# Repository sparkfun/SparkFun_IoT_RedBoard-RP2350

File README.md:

[*SparkFun IoT RedBoard - RP2350 (WRL-27708)*](https://www.sparkfun.com/sparkfun-iot-redboard-rp2350.html)

The SparkFun IoT Redboard - RP2350 combines the RP2350 microcontroller with the Raspberry Pi Radio Module 2 to provide a powerful and versatile wireless development platform in the Arduino R4 form factor. This IoT Redboard also includes integrated battery power and charging circuits, &micro;SD card slot, Qwiic connector, 3-pin debug header as well as a 22-pin ribbon cable connector tied to the RP2350's HSTX (high-speed transmit) pins. The board shares a pinout between female headers and matching 0.1"-spaced plated through-hole (PTH) headers to allow you to choose between temporary or soldered connections. 

Repository Contents
-------------------

* **/Documentation** - Data sheets, additional product information
* **/Examples** - Example code
* **/Hardware** - Eagle design files (.brd, .sch)
* **/docs** - GitHub Pages documentation files

Documentation
--------------

* **[Hookup Guide](https://docs.sparkfun.com/SparkFun_IoT_RedBoard-RP2350/)** - Basic hookup guide for the SparkFun IoT RedBoard - RP2350.

Product Versions
----------------

* [WRL-27708](https://www.sparkfun.com/sparkfun-iot-redboard-rp2350.html) - Initial release of the IoT RedBoard - RP2350

License Information
-------------------

This product is ***open source***!

Please review the LICENSE.md file for license information.

If you have any questions or concerns on licensing, please contact technical support on our [SparkFun forums](https://forum.sparkfun.com/viewforum.php?f=152).

Distributed as-is; no warranty is given.

* Your friends at SparkFun.

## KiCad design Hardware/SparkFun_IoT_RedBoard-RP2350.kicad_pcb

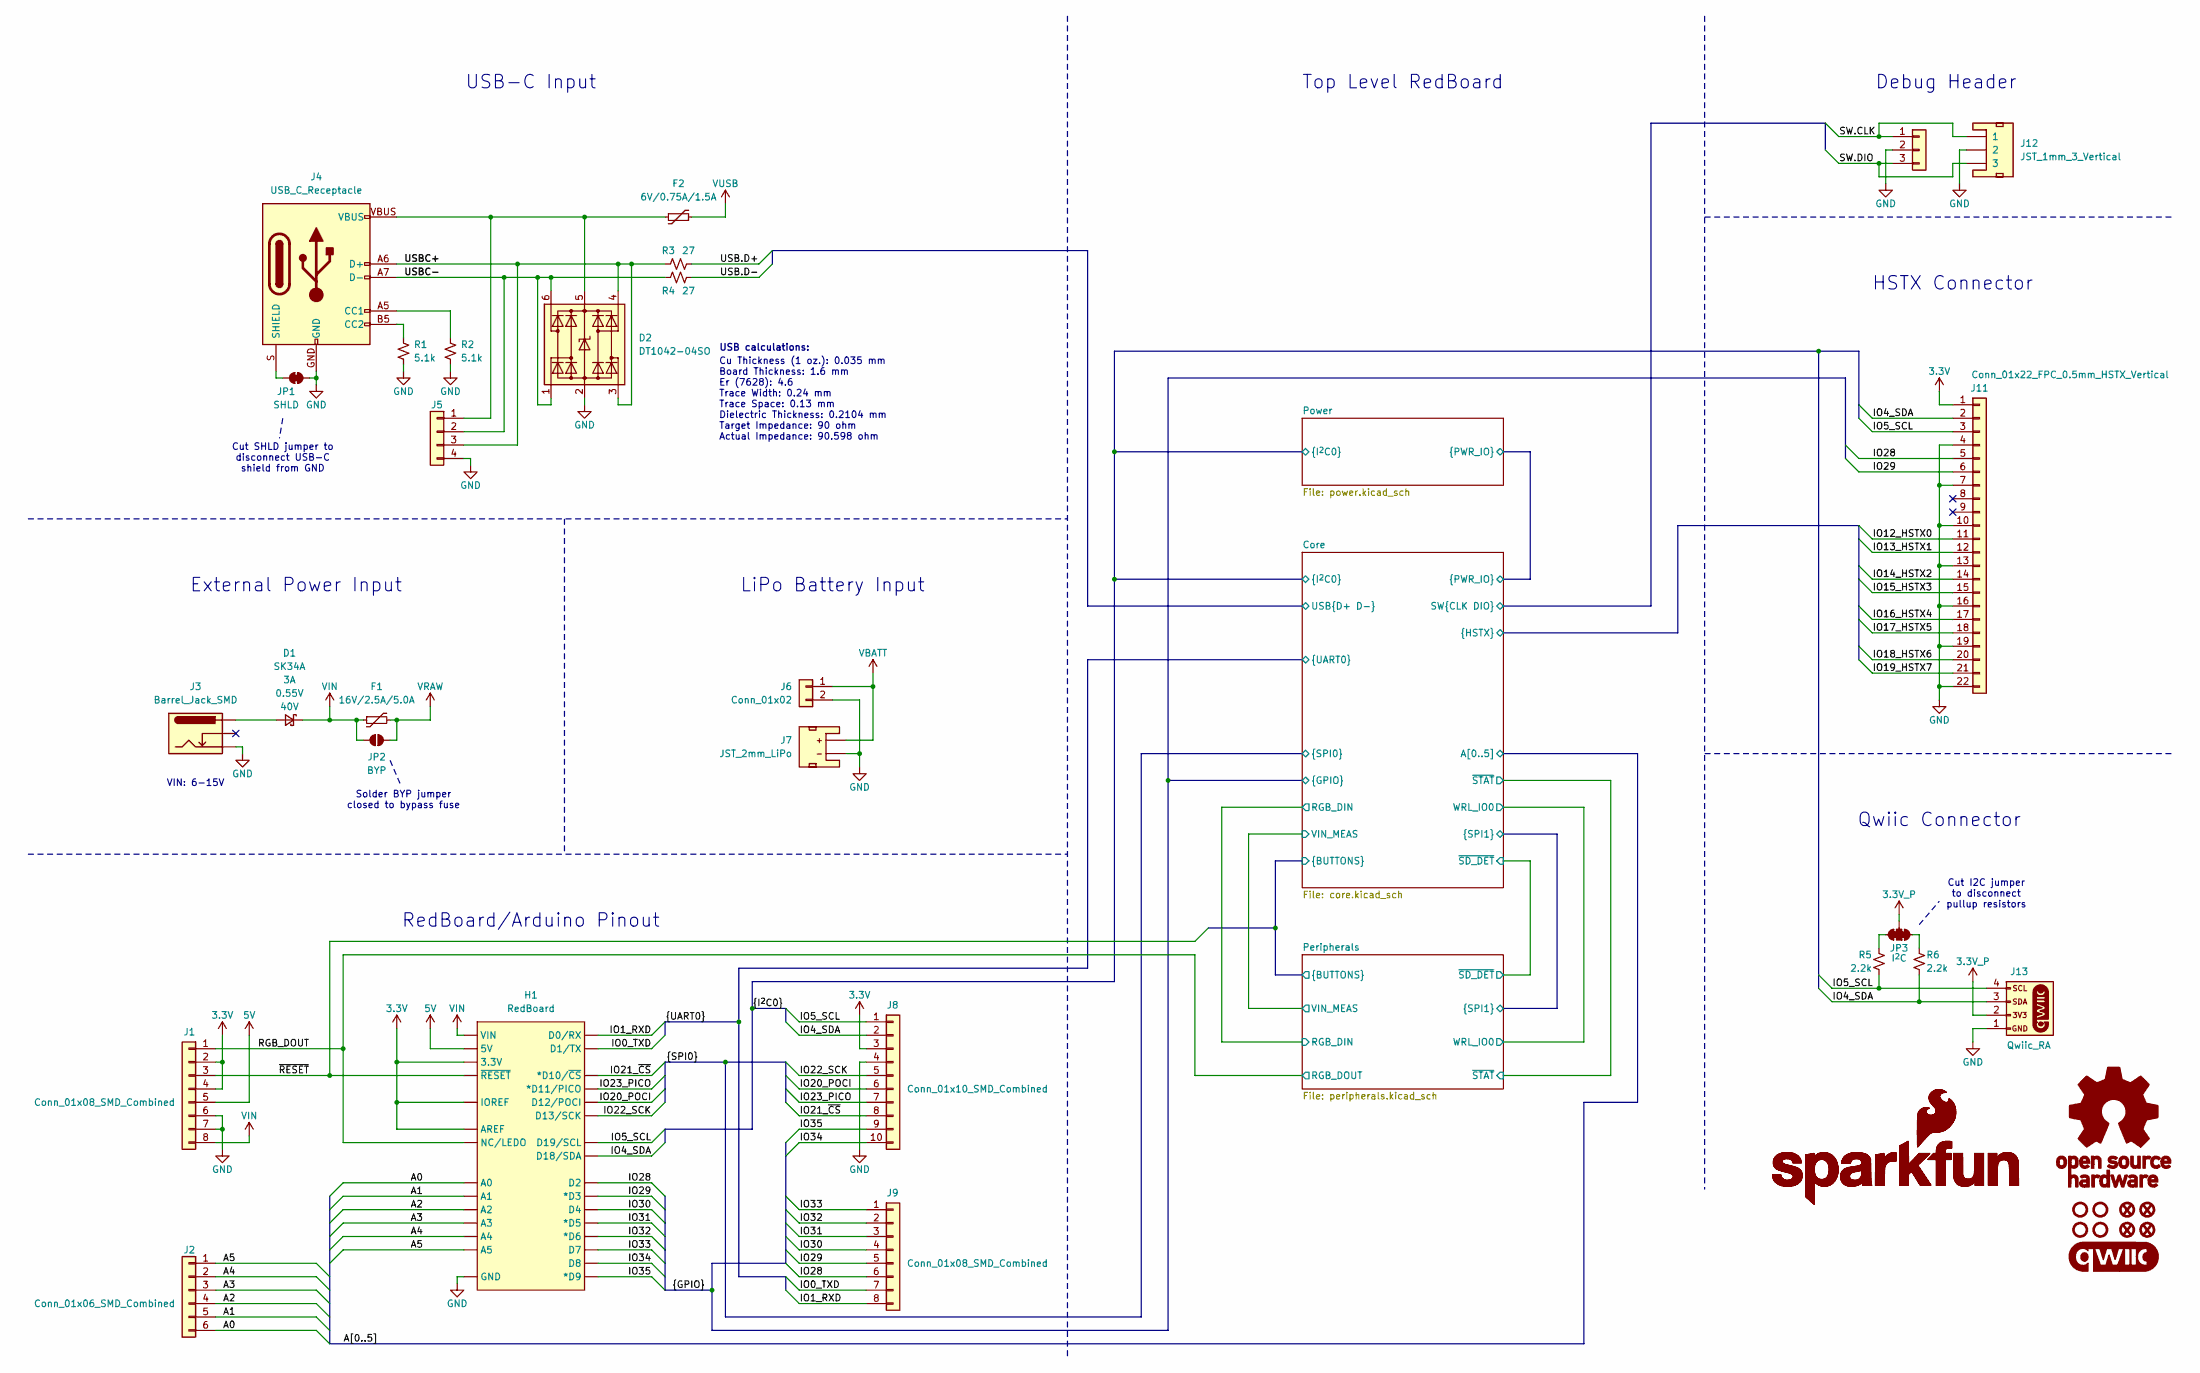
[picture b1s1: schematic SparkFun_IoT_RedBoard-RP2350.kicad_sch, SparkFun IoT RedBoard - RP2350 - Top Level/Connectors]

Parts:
D1: SK34A; SMA
D2: DT1042-04SO; SOT23-6
F1: 16V/2.5A/5.0A; 1812
F2: 6V/0.75A/1.5A; 1206
FID1, FID2, FID3, FID4: Fiducial_0.5mm; Fiducial_0.5mm_Mask1mm
G1: SparkFun_Logo; SparkFun_Logo_8mm
G2: SparkFun_Logo
G3: OSHW_Logo; Creative_Commons_License
G4: qwiic_Logo
H1: RedBoard
J1, J9: Conn_01x08_SMD_Combined; 1x08_SMD_Combined
J2: Conn_01x06_SMD_Combined; 1x06_SMD_Combined
J3: Barrel_Jack_SMD; Power_Jack_SMD
J4: USB_C_Receptacle; USB-C_16
J5: Conn_01x04_SolderPads; 1x04_Solder_Pads
J6: Conn_01x02; 1x02
J7: JST_2mm_LiPo; JST_SMD_2.0mm-2
J8: Conn_01x10_SMD_Combined; 1x10_SMD_Combined
J10: Conn_01x03; 1x03
J11: Conn_01x22_FPC_0.5mm_HSTX_Vertical; FPC_0.5mm-22_Vertical
J12: JST_1mm_3_Vertical; JST_SMD_1.0mm-3_Vertical
J13: Qwiic_RA; JST_SMD_1.0mm-4_RA
JP1: SHLD; Jumper_2_NC_Trace
JP2: BYP; Jumper_2_NO
JP3: I^{2}C; Jumper_3_NC-2_Trace
R1, R2: 5.1k; R_0402_1005Metric
R3, R4: 27; R_0402_1005Metric
R5, R6: 2.2k; R_0402_1005Metric
ST1, ST2, ST3, ST4: Standoff

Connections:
3.3V: H1.3.3V, H1.AREF, H1.IOREF, J1.2, J1.4, J8.3, J11.1; also elsewhere on the board
3.3V_P: J13.2, JP3.2 (B); also elsewhere on the board
5V: H1.5V, J1.5; also elsewhere on the board
/A0: H1.A0, J2.6; also elsewhere on the board
/A1: H1.A1, J2.5; also elsewhere on the board
/A2: H1.A2, J2.4; also elsewhere on the board
/A3: H1.A3, J2.3; also elsewhere on the board
/A4: H1.A4, J2.2; also elsewhere on the board
/A5: H1.A5, J2.1; also elsewhere on the board
/Core/IO12_HSTX0: J11.11; also elsewhere on the board
/Core/IO13_HSTX1: J11.12; also elsewhere on the board
/Core/IO14_HSTX2: J11.14; also elsewhere on the board
/Core/IO15_HSTX3: J11.15; also elsewhere on the board
/Core/IO16_HSTX4: J11.17; also elsewhere on the board
/Core/IO17_HSTX5: J11.18; also elsewhere on the board
/Core/IO18_HSTX6: J11.20; also elsewhere on the board
/Core/IO19_HSTX7: J11.21; also elsewhere on the board
/Core/SW.CLK: J10.1, J12.1; also elsewhere on the board
/Core/SW.DIO: J10.3, J12.3; also elsewhere on the board
/Core/USB.D+: R3.2; also elsewhere on the board
/Core/USB.D-: R4.2; also elsewhere on the board
/Core/~RESET: H1.~{RESET}, J1.3; also elsewhere on the board
/IO0_TXD: H1.D1 (D1/TX), J9.7; also elsewhere on the board
/IO1_RXD: H1.D0 (D0/RX), J9.8; also elsewhere on the board
/IO4_SDA: H1.D18 (D18/SDA), J8.2, J11.2, J13.3, R6.1; also elsewhere on the board
/IO5_SCL: H1.D19 (D19/SCL), J8.1, J11.3, J13.4, R5.1; also elsewhere on the board
/IO20_POCI: H1.D12 (D12/POCI), J8.6; also elsewhere on the board
/IO21_~CS: H1.D10 (*D10/~CS), J8.8; also elsewhere on the board
/IO22_SCK: H1.D13 (D13/SCK), J8.5; also elsewhere on the board
/IO23_PICO: H1.D11 (*D11/PICO), J8.7; also elsewhere on the board
/IO28: H1.D2, J9.6, J11.5; also elsewhere on the board
/IO29: H1.D3 (*D3), J9.5, J11.6; also elsewhere on the board
/IO30: H1.D4, J9.4; also elsewhere on the board
/IO31: H1.D5 (*D5), J9.3; also elsewhere on the board
/IO32: H1.D6 (*D6), J9.2; also elsewhere on the board
/IO33: H1.D7, J9.1; also elsewhere on the board
/IO34: H1.D8, J8.10; also elsewhere on the board
/IO35: H1.D9 (*D9), J8.9; also elsewhere on the board
/RGB_DOUT: H1.NC/LEDO, J1.1; also elsewhere on the board
/USBC+: D2.3 (I/O2), D2.4 (I/O3), J4.A6 (D+), J4.B6 (D+), J5.3, R3.1
/USBC-: D2.1 (I/O1), D2.6 (I/O4), J4.A7 (D-), J4.B7 (D-), J5.2, R4.1
GND: D2.2 (GND), H1.GND, J1.6, J1.7, J3.GND, J4.GND, J5.4, J6.2, J7.1 (-), J8.4, J10.2, J11.4, J11.7, J11.10, J11.13, J11.16, J11.19, J11.22, J12.2, J13.1, JP1.2 (B), R1.1, R2.1; also elsewhere on the board
unnamed: D1.A, J3.PWR
unnamed: D2.5 (VCC), F2.1, J4.VBUS, J5.1
unnamed: J4.A5 (CC1), R2.2
unnamed: J4.B5 (CC2), R1.2
unnamed: J4.S (SHIELD), JP1.1 (A)
unnamed: JP3.1 (A), R6.2
unnamed: JP3.3 (C), R5.2
VBATT: J6.1, J7.2 (+); also elsewhere on the board
VIN: D1.C (K), F1.1, H1.VIN, J1.8, JP2.1 (A)
VRAW: F1.2, JP2.2 (B); also elsewhere on the board
VUSB: F2.2; also elsewhere on the board

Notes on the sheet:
Qwiic Connector
Top Level RedBoard
Cut SHLD jumper to disconnect USB-C shield from GND
USB calculations:
VIN: 6-15V
Debug Header
External Power Input
Cut I2C jumper to disconnect pullup resistors
HSTX Connector
RedBoard/Arduino Pinout
USB-C Input
LiPo Battery Input
Cu Thickness (1 oz.): 0.035 mm Board Thickness: 1.6 mm Er (7628): 4.6 Trace Width: 0.24 mm Trace Space: 0.13 mm Dielectric Thickness: 0.2104 mm Target Impedance: 90 ohm Actual Impedance: 90.598 ohm
Solder BYP jumper closed to bypass fuse

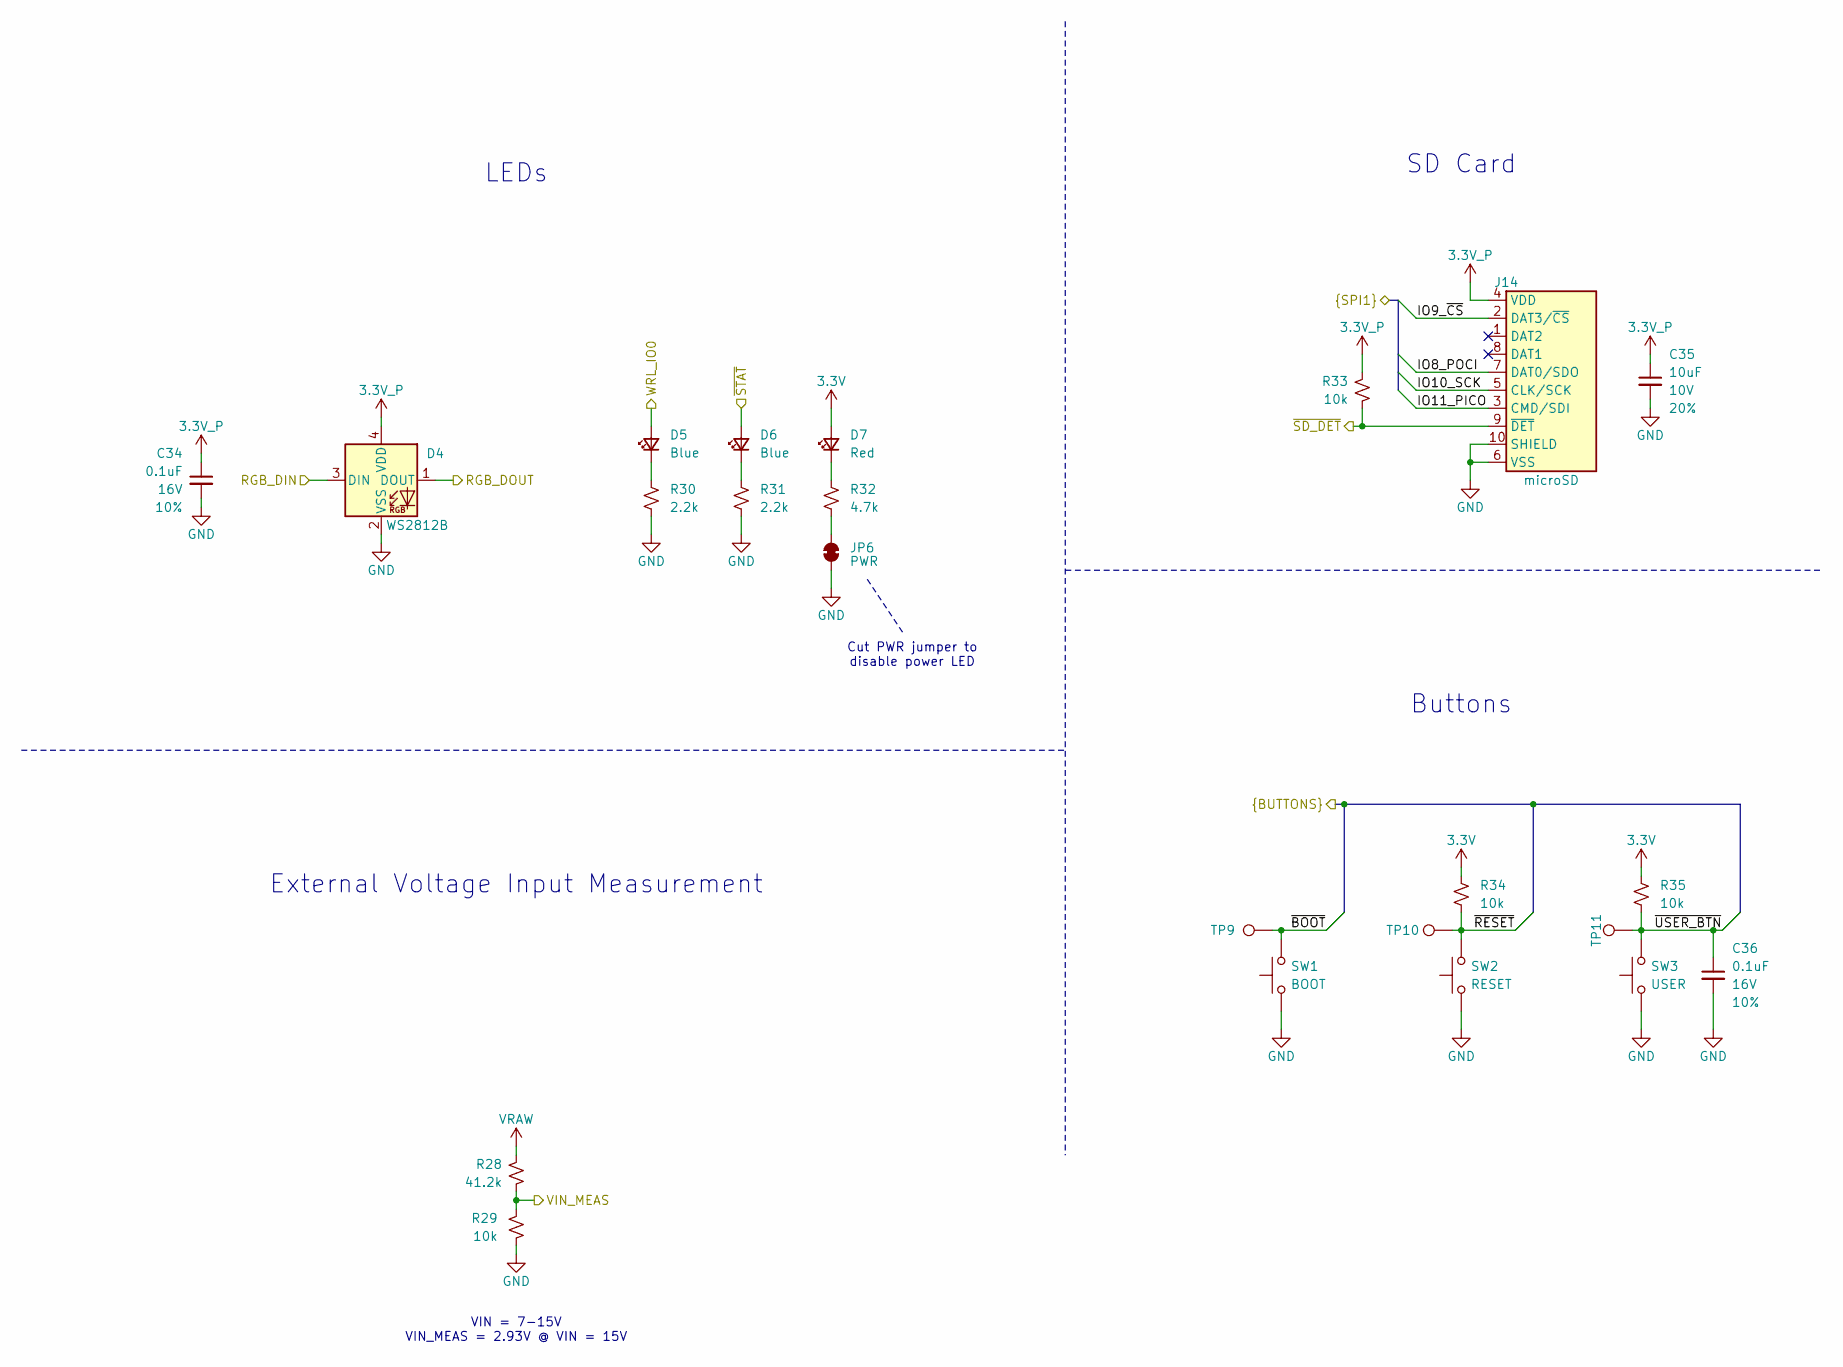
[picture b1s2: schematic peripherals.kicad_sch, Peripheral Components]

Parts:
C34, C36: 0.1uF; C_0402_1005Metric; Voltage 16V; Tolerance 10%
C35: 10uF; C_0603_1608Metric; Voltage 10V; Tolerance 20%
D4: WS2812B; WS2812_2020
D5, D6: Blue; LED_0603_1608Metric_Blue
D7: Red; LED_0603_1608Metric_Red
J14: microSD; microSD_External_Pin
JP6: PWR; Jumper_2_NC_Trace
R28: 41.2k; R_0402_1005Metric
R29, R33, R34, R35: 10k; R_0402_1005Metric
R30, R31: 2.2k; R_0402_1005Metric
R32: 4.7k; R_0402_1005Metric
SW1: BOOT; Push_SMD_5.2x5.2mm_h2.5mm
SW2: RESET; Push_SMD_5.2x5.2mm_h2.5mm
SW3: USER; Push_SMD_5.2x5.2mm_h2.5mm
TP9, TP10, TP11: 1.0mm; TestPoint-1.0mm

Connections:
3.3V: D7.2 (A), R34.2, R35.2; also elsewhere on the board
3.3V_P: C34.1, C35.1, D4.4 (VDD), J14.4 (VDD), R33.2; also elsewhere on the board
/Core/IO8_POCI: J14.7 (DAT0/SDO); also elsewhere on the board
/Core/IO9_~CS: J14.2 (DAT3/~CS); also elsewhere on the board
/Core/IO10_SCK: J14.5 (CLK/SCK); also elsewhere on the board
/Core/IO11_PICO: J14.3 (CMD/SDI); also elsewhere on the board
/Core/RGB_DIN: D4.3 (DIN); also elsewhere on the board
/Core/VIN_MEAS: R28.1, R29.2; also elsewhere on the board
/Core/WRL_IO0: D5.2 (A); also elsewhere on the board
/Core/~BOOT: SW1.2, TP9.1; also elsewhere on the board
/Core/~RESET: R34.1, SW2.2, TP10.1; also elsewhere on the board
/Core/~SD_DET: J14.9 (~DET), R33.1; also elsewhere on the board
/Core/~STAT: D6.2 (A); also elsewhere on the board
/Core/~USER_BTN: C36.1, R35.1, SW3.2, TP11.1; also elsewhere on the board
/RGB_DOUT: D4.1 (DOUT); also elsewhere on the board
GND: C34.2, C35.2, C36.2, D4.2 (VSS), J14.6 (VSS), J14.10 (SHIELD), JP6.1 (A), R29.1, R30.1, R31.1, SW1.1, SW2.1, SW3.1; also elsewhere on the board
unnamed: D5.1 (K), R30.2
unnamed: D6.1 (K), R31.2
unnamed: D7.1 (K), R32.2
unnamed: JP6.2 (B), R32.1
VRAW: R28.2; also elsewhere on the board

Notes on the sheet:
Buttons
VIN = 7-15V VIN_MEAS = 2.93V @ VIN = 15V
SD Card
Cut PWR jumper to disable power LED
LEDs
External Voltage Input Measurement

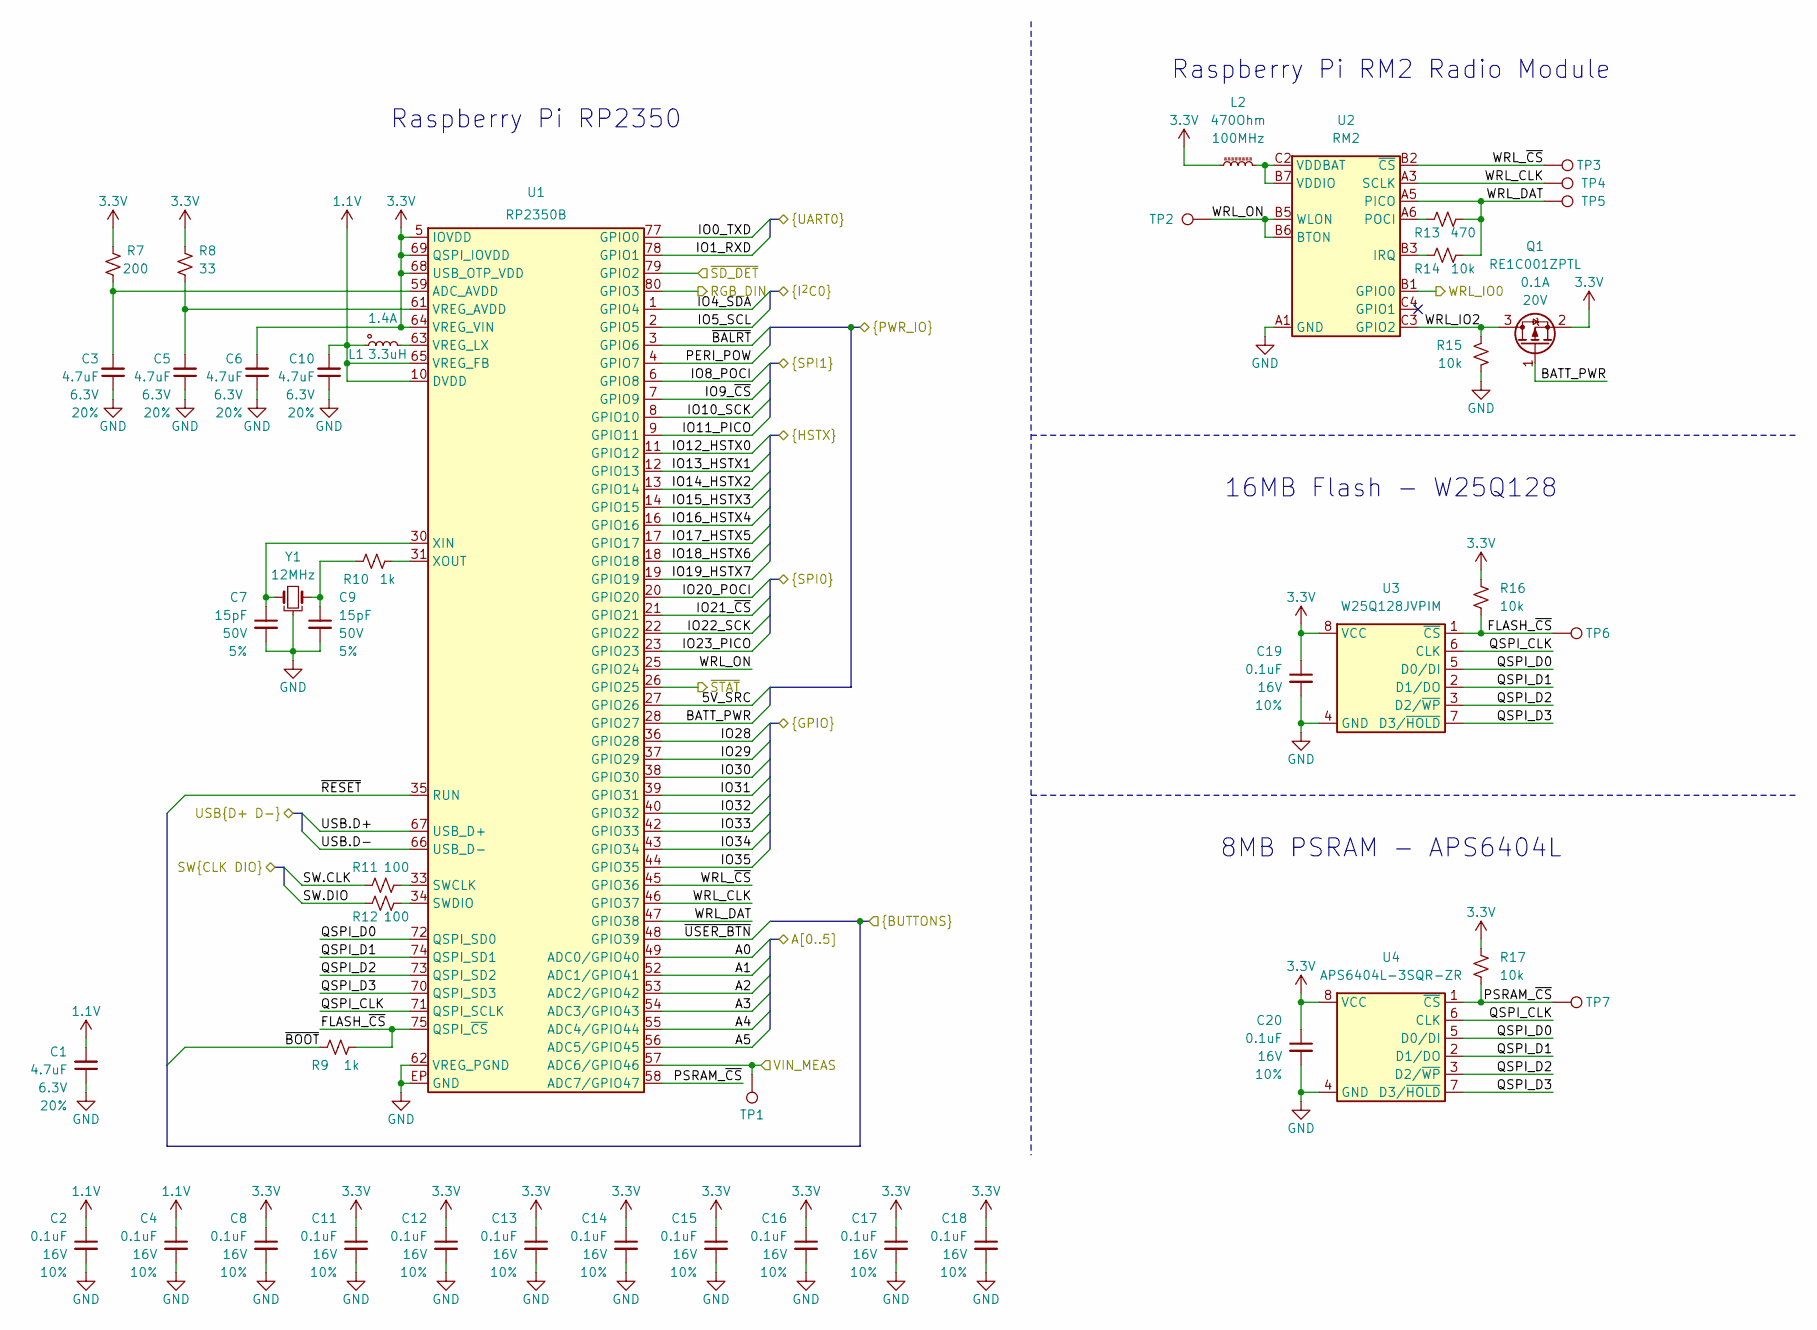
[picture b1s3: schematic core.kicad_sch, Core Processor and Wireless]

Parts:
C1, C3, C5, C6, C10: 4.7uF; C_0402_1005Metric; Voltage 6.3V; Tolerance 20%
C2, C4, C8, C11, C12, C13, C14, C15, C16, C17, C18, C19, C20: 0.1uF; C_0402_1005Metric; Voltage 16V; Tolerance 10%
C7, C9: 15pF; C_0402_1005Metric; Voltage 50V; Tolerance 5%
L1: 3.3uH; 0806_Polarized
L2: 470Ohm; C_0603_1608Metric
Q1: RE1C001ZPTL; SC-89 SOT-490
R7: 200; R_0402_1005Metric
R8: 33; R_0402_1005Metric
R9, R10: 1k; R_0402_1005Metric
R11, R12: 100; R_0402_1005Metric
R13: 470; R_0402_1005Metric
R14, R15, R16, R17: 10k; R_0402_1005Metric
TP1, TP2, TP3, TP4, TP5, TP6, TP7: 1.0mm; TestPoint-1.0mm
U1: RP2350B; QFN-80-1EP_10x10mm_P0.4mm_EP3.4x3.4mm
U2: RM2; RM2_Tight
U3: W25Q128JVPIM; WDFN-8_6x5mm-SkinnyCenterPad
U4: APS6404L-3SQR-ZR; USON-8_3x2mm-SkinnyCenterPad
Y1: 12MHz; Crystal_SMD_2.5x2.0mm

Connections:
1.1V: C1.2, C2.1, C4.1, C10.2, L1.1, U1.10 (DVDD), U1.32 (DVDD), U1.51 (DVDD), U1.65 (VREG_FB)
3.3V: C6.2, C8.1, C11.1, C12.1, C13.1, C14.1, C15.1, C16.1, C17.1, C18.1, C19.1, C20.1, L2.1, Q1.2 (S), R7.2, R8.2, R16.2, R17.2, U1.5 (IOVDD), U1.15 (IOVDD), U1.24 (IOVDD), U1.29 (IOVDD), U1.41 (IOVDD), U1.50 (IOVDD), U1.60 (IOVDD), U1.64 (VREG_VIN), U1.68 (USB_OTP_VDD), U1.69 (QSPI_IOVDD), U1.76 (IOVDD), U3.8 (VCC), U4.8 (VCC); also elsewhere on the board
/A0: U1.49 (ADC0/GPIO40); also elsewhere on the board
/A1: U1.52 (ADC1/GPIO41); also elsewhere on the board
/A2: U1.53 (ADC2/GPIO42); also elsewhere on the board
/A3: U1.54 (ADC3/GPIO43); also elsewhere on the board
/A4: U1.55 (ADC4/GPIO44); also elsewhere on the board
/A5: U1.56 (ADC5/GPIO45); also elsewhere on the board
/Core/5V_SRC: U1.27 (GPIO26); also elsewhere on the board
/Core/BATT_PWR: Q1.1 (G), U1.28 (GPIO27); also elsewhere on the board
/Core/FLASH_~CS: R9.1, R16.1, TP6.1, U1.75 (QSPI_~CS), U3.1 (~CS)
/Core/IO8_POCI: U1.6 (GPIO8); also elsewhere on the board
/Core/IO9_~CS: U1.7 (GPIO9); also elsewhere on the board
/Core/IO10_SCK: U1.8 (GPIO10); also elsewhere on the board
/Core/IO11_PICO: U1.9 (GPIO11); also elsewhere on the board
/Core/IO12_HSTX0: U1.11 (GPIO12); also elsewhere on the board
/Core/IO13_HSTX1: U1.12 (GPIO13); also elsewhere on the board
/Core/IO14_HSTX2: U1.13 (GPIO14); also elsewhere on the board
/Core/IO15_HSTX3: U1.14 (GPIO15); also elsewhere on the board
/Core/IO16_HSTX4: U1.16 (GPIO16); also elsewhere on the board
/Core/IO17_HSTX5: U1.17 (GPIO17); also elsewhere on the board
/Core/IO18_HSTX6: U1.18 (GPIO18); also elsewhere on the board
/Core/IO19_HSTX7: U1.19 (GPIO19); also elsewhere on the board
/Core/PERI_POW: U1.4 (GPIO7); also elsewhere on the board
/Core/PSRAM_~CS: R17.1, TP7.1, U1.58 (ADC7/GPIO47), U4.1 (~CS)
/Core/QSPI_CLK: U1.71 (QSPI_SCLK), U3.6 (CLK), U4.6 (CLK)
/Core/QSPI_D0: U1.72 (QSPI_SD0), U3.5 (D0/DI), U4.5 (D0/DI)
/Core/QSPI_D1: U1.74 (QSPI_SD1), U3.2 (D1/DO), U4.2 (D1/DO)
/Core/QSPI_D2: U1.73 (QSPI_SD2), U3.3 (D2/~WP), U4.3 (D2/~WP)
/Core/QSPI_D3: U1.70 (QSPI_SD3), U3.7 (D3/~HOLD), U4.7 (D3/~HOLD)
/Core/RGB_DIN: U1.80 (GPIO3); also elsewhere on the board
/Core/SW.CLK: R11.1; also elsewhere on the board
/Core/SW.DIO: R12.1; also elsewhere on the board
/Core/USB.D+: U1.67 (USB_D+); also elsewhere on the board
/Core/USB.D-: U1.66 (USB_D-); also elsewhere on the board
/Core/VIN_MEAS: TP1.1, U1.57 (ADC6/GPIO46); also elsewhere on the board
/Core/WRL_CLK: TP4.1, U1.46 (GPIO37), U2.A3 (SCLK)
/Core/WRL_DAT: R13.2, R14.2, TP5.1, U1.47 (GPIO38), U2.A5 (PICO)
/Core/WRL_IO0: U2.B1 (GPIO0); also elsewhere on the board
/Core/WRL_IO2: Q1.3 (D), R15.2, U2.C3 (GPIO2)
/Core/WRL_ON: TP2.1, U1.25 (GPIO24), U2.B5 (WLON), U2.B6 (BTON)
/Core/WRL_~CS: TP3.1, U1.45 (GPIO36), U2.B2 (~CS)
/Core/~BALRT: U1.3 (GPIO6); also elsewhere on the board
/Core/~BOOT: R9.2; also elsewhere on the board
/Core/~RESET: U1.35 (RUN); also elsewhere on the board
/Core/~SD_DET: U1.79 (GPIO2); also elsewhere on the board
/Core/~STAT: U1.26 (GPIO25); also elsewhere on the board
/Core/~USER_BTN: U1.48 (GPIO39); also elsewhere on the board
/IO0_TXD: U1.77 (GPIO0); also elsewhere on the board
/IO1_RXD: U1.78 (GPIO1); also elsewhere on the board
/IO4_SDA: U1.1 (GPIO4); also elsewhere on the board
/IO5_SCL: U1.2 (GPIO5); also elsewhere on the board
/IO20_POCI: U1.20 (GPIO20); also elsewhere on the board
/IO21_~CS: U1.21 (GPIO21); also elsewhere on the board
/IO22_SCK: U1.22 (GPIO22); also elsewhere on the board
/IO23_PICO: U1.23 (GPIO23); also elsewhere on the board
/IO28: U1.36 (GPIO28); also elsewhere on the board
/IO29: U1.37 (GPIO29); also elsewhere on the board
/IO30: U1.38 (GPIO30); also elsewhere on the board
/IO31: U1.39 (GPIO31); also elsewhere on the board
/IO32: U1.40 (GPIO32); also elsewhere on the board
/IO33: U1.42 (GPIO33); also elsewhere on the board
/IO34: U1.43 (GPIO34); also elsewhere on the board
/IO35: U1.44 (GPIO35); also elsewhere on the board
GND: C1.1, C2.2, C3.1, C4.2, C5.1, C6.1, C7.2, C8.2, C9.2, C10.1, C11.2, C12.2, C13.2, C14.2, C15.2, C16.2, C17.2, C18.2, C19.2, C20.2, R15.1, U1.62 (VREG_PGND), U1.EP (GND), U2.A1 (GND), U2.A4 (GND), U2.A7 (GND), U2.B4 (GND), U2.C1 (GND), U2.C7 (GND), U3.4 (GND), U3.EPAD (GND), U4.4 (GND), U4.9 (GND), Y1.2, Y1.4; also elsewhere on the board
unnamed: C9.1, R10.1, Y1.3
unnamed: C3.2, R7.1, U1.59 (ADC_AVDD)
unnamed: R11.2, U1.33 (SWCLK)
unnamed: R12.2, U1.34 (SWDIO)
unnamed: C5.2, R8.1, U1.61 (VREG_AVDD)
unnamed: L1.2, U1.63 (VREG_LX)
unnamed: C7.1, U1.30 (XIN), Y1.1
unnamed: R10.2, U1.31 (XOUT)
unnamed: R14.1, U2.B3 (IRQ)
unnamed: R13.1, U2.A6 (POCI)
unnamed: L2.2, U2.B7 (VDDIO), U2.C2 (VDDBAT)

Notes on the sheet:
16MB Flash - W25Q128
8MB PSRAM - APS6404L
Raspberry Pi RP2350
Raspberry Pi RM2 Radio Module

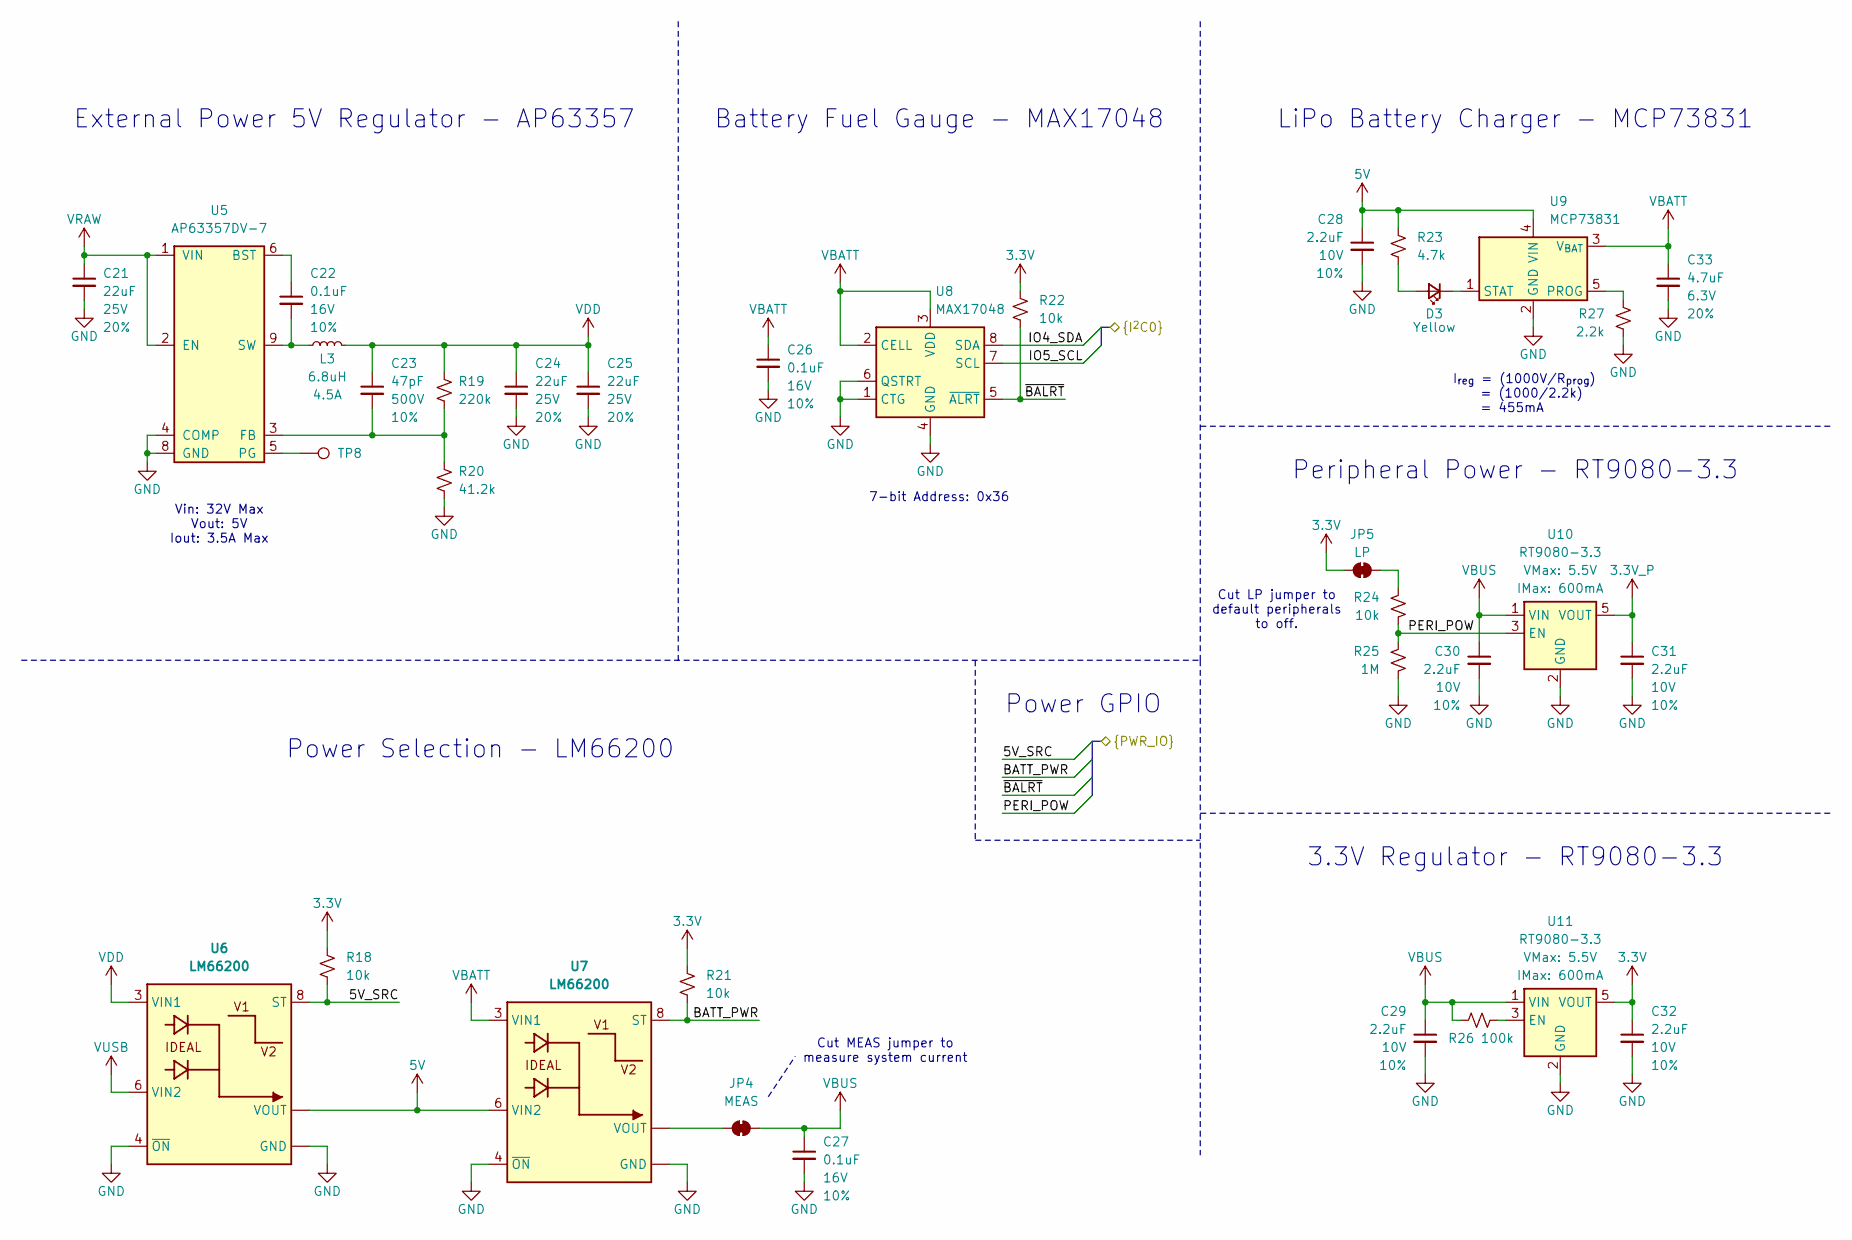
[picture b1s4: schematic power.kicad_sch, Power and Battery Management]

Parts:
C21, C24, C25: 22uF; C_0805_2012Metric; Voltage 25V; Tolerance 20%
C22, C26, C27: 0.1uF; C_0402_1005Metric; Voltage 16V; Tolerance 10%
C23: 47pF; C_0402_1005Metric; Voltage 500V; Tolerance 10%
C28, C29, C30, C31, C32: 2.2uF; C_0402_1005Metric; Voltage 10V; Tolerance 10%
C33: 4.7uF; C_0402_1005Metric; Voltage 6.3V; Tolerance 20%
D3: Yellow; LED_0603_1608Metric_Yellow
JP4: MEAS; Jumper_2_PTH_SMD_Combo-NC
JP5: LP; Jumper_2_NC_Trace
L3: 6.8uH; Inductor_7.3x6.6mm
R18, R21, R22, R24: 10k; R_0402_1005Metric
R19: 220k; R_0402_1005Metric
R20: 41.2k; R_0402_1005Metric
R23: 4.7k; R_0402_1005Metric
R25: 1M; R_0402_1005Metric
R26: 100k; R_0402_1005Metric
R27: 2.2k; R_0402_1005Metric
TP8: 1.0mm; TestPoint-1.0mm
U5: AP63357DV-7; PowerVFDFN-13
U6, U7: LM66200; SOT-583-8
U8: MAX17048; DFN-8
U9: MCP73831; SOT23-5
U10, U11: RT9080-3.3; SOT23-5

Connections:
3.3V: C32.1, JP5.1 (A), R18.2, R21.2, R22.2, U11.5 (VOUT); also elsewhere on the board
3.3V_P: C31.1, U10.5 (VOUT); also elsewhere on the board
5V: C28.1, R23.2, U6.2 (VOUT), U6.7 (VOUT), U7.6 (VIN2), U9.4 (VIN); also elsewhere on the board
/Core/5V_SRC: R18.1, U6.8 (ST); also elsewhere on the board
/Core/BATT_PWR: R21.1, U7.8 (ST); also elsewhere on the board
/Core/PERI_POW: R24.2, R25.2, U10.3 (EN); also elsewhere on the board
/Core/~BALRT: R22.1, U8.5 (~ALRT); also elsewhere on the board
/IO4_SDA: U8.8 (SDA); also elsewhere on the board
/IO5_SCL: U8.7 (SCL); also elsewhere on the board
GND: C21.2, C24.2, C25.2, C26.2, C27.2, C28.2, C29.2, C30.2, C31.2, C32.2, C33.2, R20.1, R25.1, R27.1, U5.4 (COMP), U5.8 (GND), U6.1 (GND), U6.4 (~ON), U6.5 (GND), U7.1 (GND), U7.4 (~ON), U7.5 (GND), U8.1 (CTG), U8.4 (GND), U8.6 (QSTRT), U8.9 (GND), U9.2 (GND), U10.2 (GND), U11.2 (GND); also elsewhere on the board
unnamed: D3.2 (A), R23.1
unnamed: D3.1 (K), U9.1 (STAT)
unnamed: JP4.1 (A), U7.2 (VOUT), U7.7 (VOUT)
unnamed: JP5.2 (B), R24.1
unnamed: C22.1, U5.6 (BST)
unnamed: C23.2, R19.1, R20.2, U5.3 (FB)
unnamed: C22.2, L3.1, U5.7 (NC), U5.9 (SW)
unnamed: TP8.1, U5.5 (PG)
unnamed: R27.2, U9.5 (PROG)
unnamed: R26.2, U11.3 (EN)
VBATT: C26.1, C33.1, U7.3 (VIN1), U8.2 (CELL), U8.3 (VDD), U9.3 (V_{BAT}); also elsewhere on the board
VBUS: C27.1, C29.1, C30.1, JP4.2 (B), R26.1, U10.1 (VIN), U11.1 (VIN)
VDD: C23.1, C24.1, C25.1, L3.2, R19.2, U6.3 (VIN1)
VRAW: C21.1, U5.1 (VIN), U5.2 (EN); also elsewhere on the board
VUSB: U6.6 (VIN2); also elsewhere on the board

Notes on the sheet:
Cut LP jumper to default peripherals to off.
Power Selection - LM66200
Battery Fuel Gauge - MAX17048
I_{reg} = (1000V/R_{prog}) = (1000/2.2k) = 455mA
External Power 5V Regulator - AP63357
3.3V Regulator - RT9080-3.3
Power GPIO
LiPo Battery Charger - MCP73831
Peripheral Power - RT9080-3.3
Vin: 32V Max Vout: 5V Iout: 3.5A Max
Cut MEAS jumper to measure system current
7-bit Address: 0x36

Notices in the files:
parts and their libraries:
Released under the Creative Commons Attribution Share-Alike 4.0 License
https://creativecommons.org/licenses/by-sa/4.0
